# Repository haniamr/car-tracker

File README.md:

Car Tracker
===========

Car tracker that is build using python over Telit GM862-GPS module. It is designed to interpret SMS messages to do commands as getting the location and stop the vehicle.

The commands format in SMS are:

1. SETPWD <PASSWORD>  //Command that is used to set the password for the first time.
2. GL <PASSWORD>      //Stands for get location and it should return a link to Google Maps with the proper coordinates.
3. STP  <PASSWORD>    //Issues the command to stop the vehicle which in turn gives 1 on GPIO pin 8.
4. STRT <PASSWORD>    //Issues the command to enable the vehicle to start normally by giving 0 on GPIO pin 8.
5. DELALL <PASSWORD>  //Deletes all messages including the password. Therefore, a SETPWD must be issued again.
6. UPD    <PASSWORD>  //NOT YET TESTED. Should allow the user to update the code on the module over the air.

The code is designed to interpret only SMS messages but the module is capable of having sockets to listen and therefore you can call it from a mobile application to ease the user experience.

The code simply issues AT commands to communicate with the hardware and the circuit design can be found in folder named "Locus".

Things to buy for the circuit that may not be clearly stated in the schematics:

1. N-Channel MOSFET: https://www.sparkfun.com/products/10213
2. SparkFun 50-pin evaluation board for GM862-GPS. It's currently obsolete, you can search for replacements as this one http://www.mikroe.com/products/view/469/smartgm862-gps-board/ or design your own using the SMD connector https://www.sparkfun.com/products/283.

The circuit exposes "Source" and "Drain" for the MOSFET used and then you should connect those to the fuel-pump relay in the vehicle in order to have a fully-functional device that can track the location and stop the vehicle.

I'd be glad to assist anyone and contributors are most welcomed!

CREDITS
=======
1. Islam Khattab.
2. Mohamed Omar.
3. Hani Amr.

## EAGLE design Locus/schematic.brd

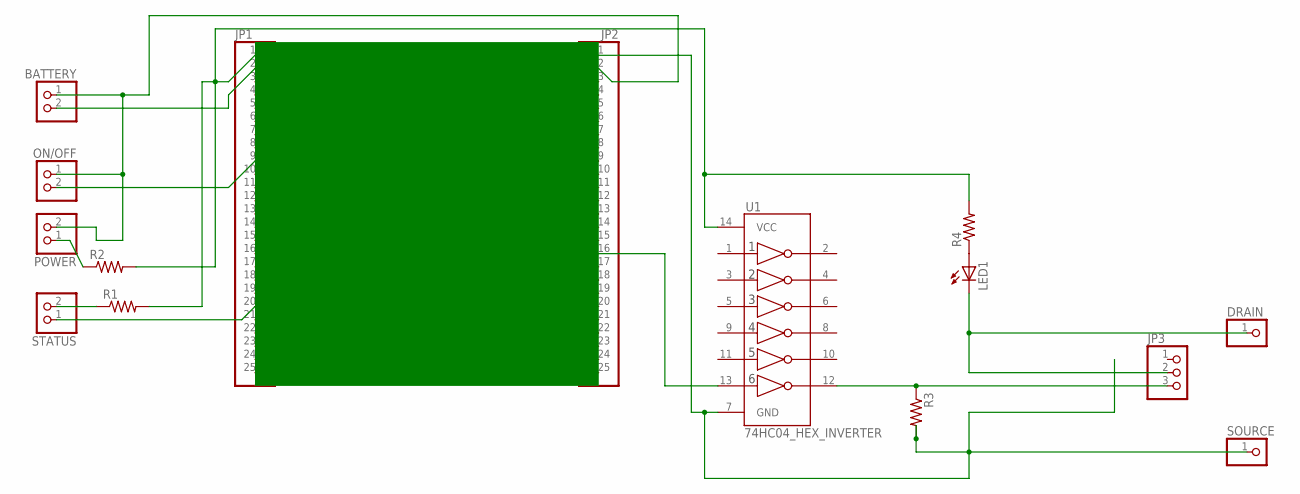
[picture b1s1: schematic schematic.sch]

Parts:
BATTERY: PINHD-1X2; 1X02
DRAIN: PINHD-1X1; 1X01
JP1, JP2: PINHD-1X25; 1X25
JP3: PINHD-1X3; 1X03
LED1: LED-3MM-NO_SILK; LED3MM-NS
ON/OFF: PINHD-1X2; 1X02
POWER: PINHD-1X2; 1X02
R1, R2, R3, R4: RESISTORKIT; AXIAL-0.3-KIT
SOURCE: PINHD-1X1; 1X01
STATUS: PINHD-1X2; 1X02
U1: 74HC04_HEX_INVERTER; DIL14

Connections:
unnamed: JP1.20, STATUS.1
unnamed: R1.P$1 (1), STATUS.2
unnamed: BATTERY.1, JP2.2, ON/OFF.1, POWER.2
unnamed: JP1.1, R1.P$2 (2), R2.P$2 (2), R4.P$2 (2), U1.14 (VCC)
unnamed: BATTERY.2, JP1.2
unnamed: JP1.9, ON/OFF.2
unnamed: JP2.16, U1.13 (6A)
unnamed: POWER.1, R2.P$1 (1)
unnamed: JP2.1, JP3.1, R3.P$2 (2), SOURCE.1, U1.7 (GND)
unnamed: JP3.3, R3.P$1 (1), U1.12 (6Y)
unnamed: DRAIN.1, JP3.2, LED1.K (C)
unnamed: LED1.A, R4.P$1 (1)

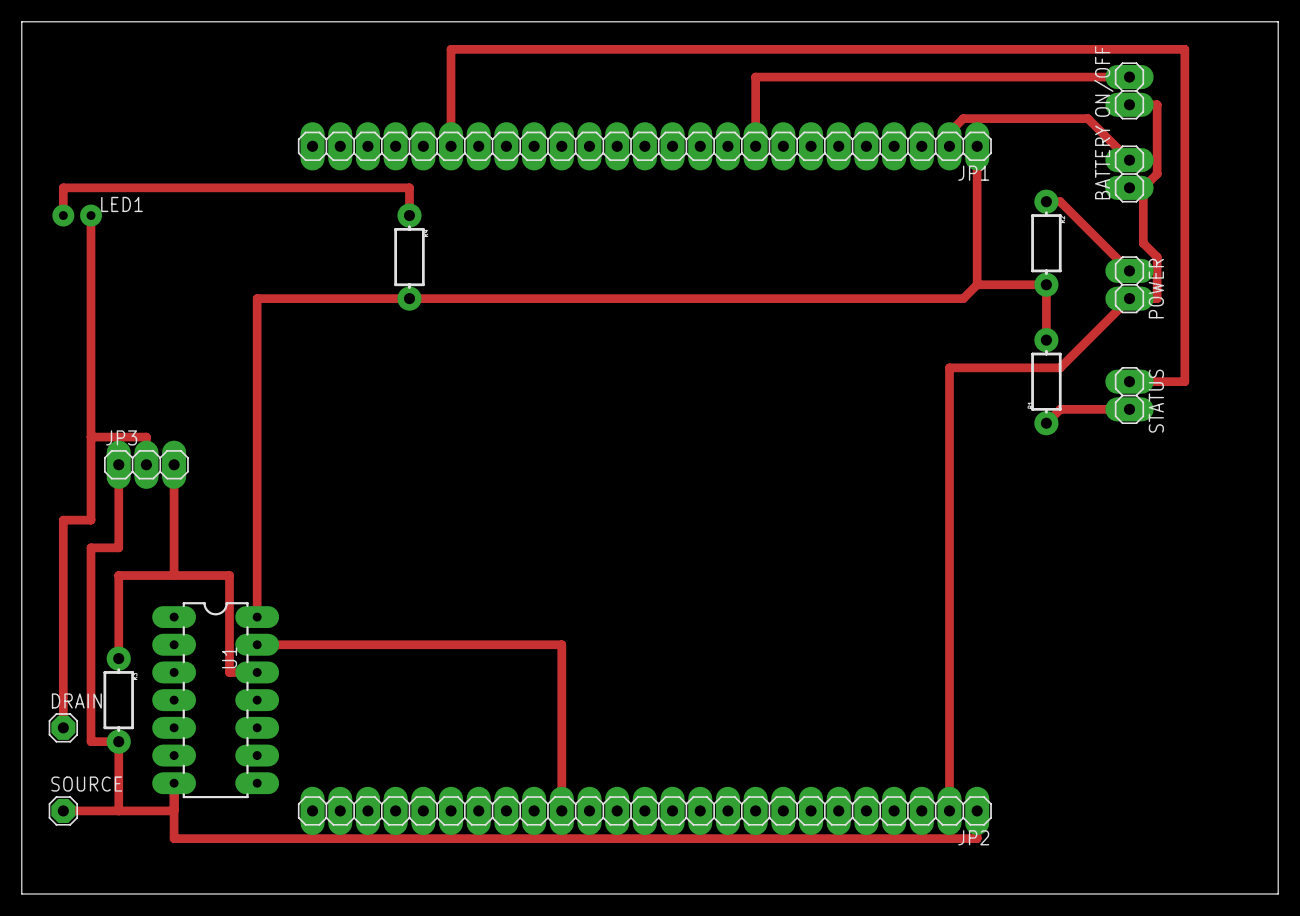
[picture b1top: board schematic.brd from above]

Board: 2 copper layers, 115.2 x 80.0 mm, 15 parts (0 on the bottom side), 12 nets.

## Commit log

2014-01-16 SMS Handler
2014-01-16 Helper functions
2014-01-16 Board design and schematics [Eagle format]
2014-01-16 Telit GM862-GPS Documentation
    Including Python and AT Commands.
2014-01-16 README
2014-01-16 Main
2014-07-24 Request Handler

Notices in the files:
parts and their libraries:
SparkFun: Licensing: CC v3.0 Share-Alike You are welcome to use this library for commercial purposes.
